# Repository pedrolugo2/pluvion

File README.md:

PLUVI.ON
--------

Como bons paulistanos, passamos pela mesma situação todos os anos. Chega dezembro, o céu escurece, a gente ouve um trovão lá no fundo, já dá aquele gelo na espinha pq a gente sabe que vem uma tempestade e provavelmente uma enchente por aí... E esse tipo de problema não acontece só em SP. 

Se olharmos Brasil, existem aproximadamente **30 milhões de brasileiros** expostos ao risco de enchentes e inundações. Além disso, existe uma projeção de impacto financeiro, onde as potenciais perdas anuais podem chegar a **4 bilhões de dólares até 2030** *(Fonte: Swiss Re)*

Olhando pra esse cenário alarmante, pensamos:
 “Vamos tentar resolver essa %$#@?” Se não para resolver totalmente, pelo menos entregar mais informação, mais inteligência para que a população possa se prevenir nesses eventos?
Resolvemos juntar nosso conhecimento de hardware e software e mergulhamos nesse mundo e logo de cara demos de cara com uma barreira: as dificuldades de conseguir informações sobre clima e chuva
Identificamos **3 principais desafios** relacionados à informação:

 1. As informações históricas são de difícil acesso ao cidadão comum (ou
    estão em mão de instituições privadas ou demandam muita burocracia
    dos órgãos públicos);
    
 2. Muitas delas são coletadas apenas no dia seguinte e portanto não auxiliam na
    prevenção 
    
 3. São informadas de forma genérica: “pode alagar a cidade de
    SP” – mas SP é grande demais para termos apenas essa informação. A
    probabilidade de alagar a Av. Paulista é sempre muito menor do que
    alagar a Av. Aricanduva

Foi a partir dessas hipóteses que construímos o Pluvi.On, uma estação meteorológica Open Source e de baixo custo para ser espalhada na maior quantidade de pontos da cidade que pudermos!!!

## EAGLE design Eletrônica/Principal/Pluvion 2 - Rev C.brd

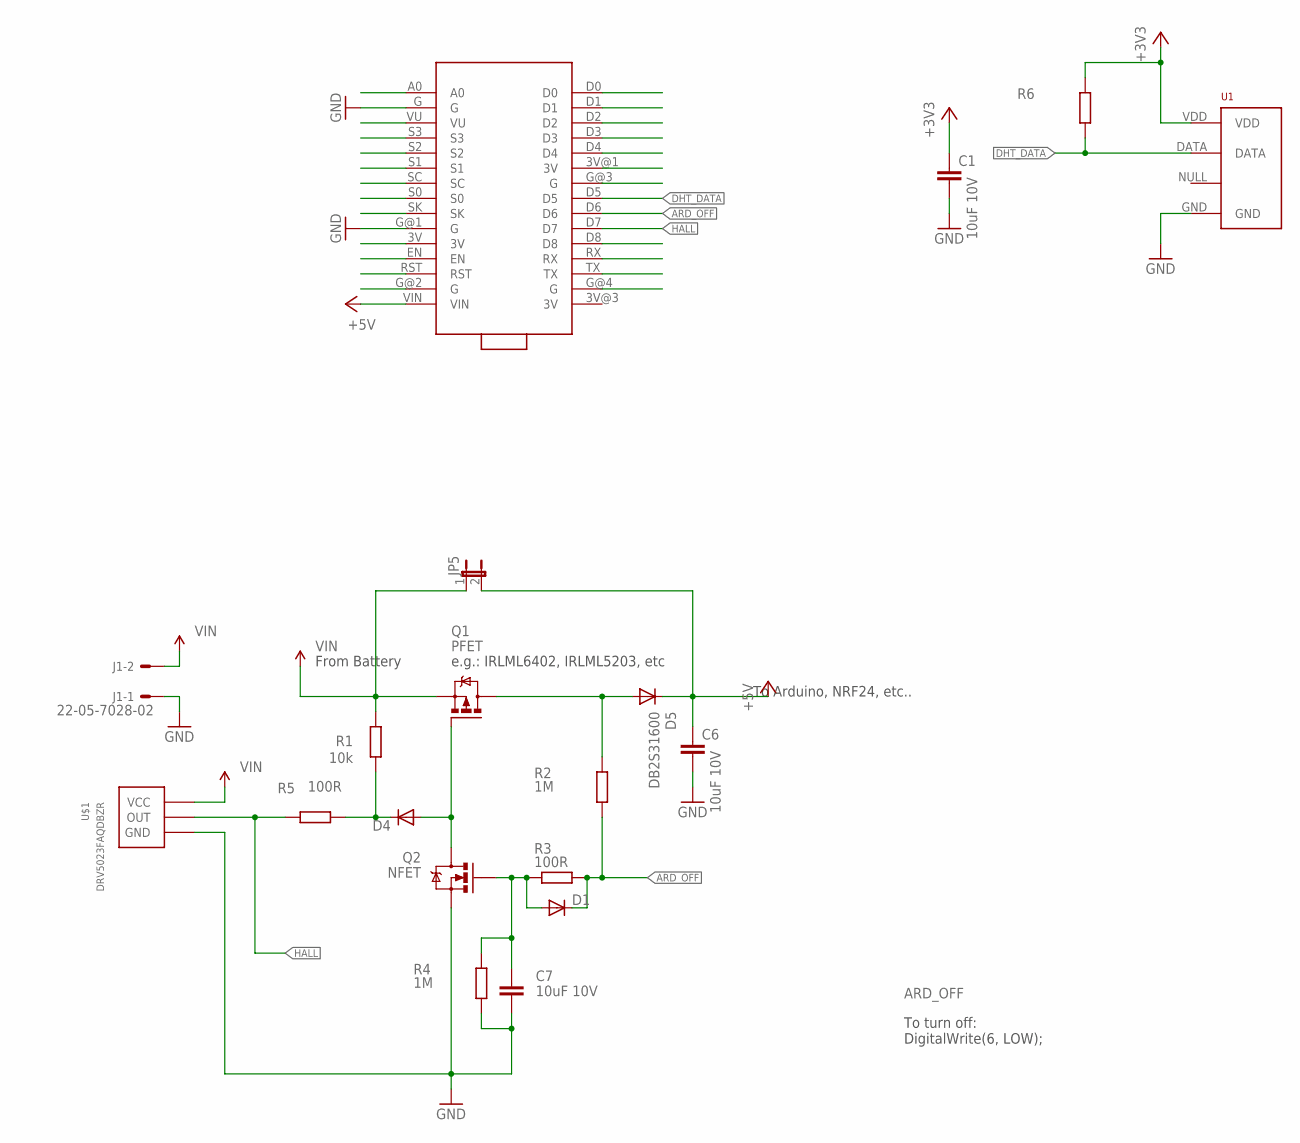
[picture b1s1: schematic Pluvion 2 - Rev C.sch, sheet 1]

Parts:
C1, C6, C7: 10uF 10V; C0805
D1, D4: DIODESOD; SOD-323
D5: DB2S31600; SMA-DIODE
J1: 22-05-7028-02; 7395-02
JP5: JUMPER-2PTH; 1X02
Q1: PFET; MICRO3
Q2: NFET; SOT23
R1: 10k; R0805
R2, R4: 1M; R0805
R3, R5: 100R; R0805
R6: R-EU_R0805; R0805
U1: RHT03_DHT-22_AM2302RA; RHT03_DHT-22/RA
U$1: DRV5023FAQDBZR; SOT23
U$2: NODE-LOLIN-ESP8266

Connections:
+3V3: C1.1, R6.2, U1.VDD, U$2.3V@1 (3V)
+5V: C6.1, D5.C, JP5.2, U$2.VIN
ARD_OFF: D1.1 (C), R2.1, R3.2, U$2.D6
BUTTONS: D4.2 (A), Q1.1 (G), Q2.3 (D)
DHT_DATA: R6.1, U1.DATA, U$2.D5
GND: C1.2, C6.2, C7.2, J1.1, Q2.2 (S), R4.1, U1.GND, U$1.3 (GND), U$2.G, U$2.G@1 (G)
HALL: R5.2, U$1.2 (OUT), U$2.D7
unnamed: D5.A, Q1.3 (D), R2.2
unnamed: C7.1, D1.2 (A), Q2.1 (G), R3.1, R4.2
unnamed: D4.1 (C), R1.1, R5.1
VIN: J1.2, JP5.1, Q1.2 (S), R1.2, U$1.1 (VCC)

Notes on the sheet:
e.g.: IRLML6402, IRLML5203, etc
To Arduino, NRF24, etc..
To turn off: DigitalWrite(6, LOW);
From Battery

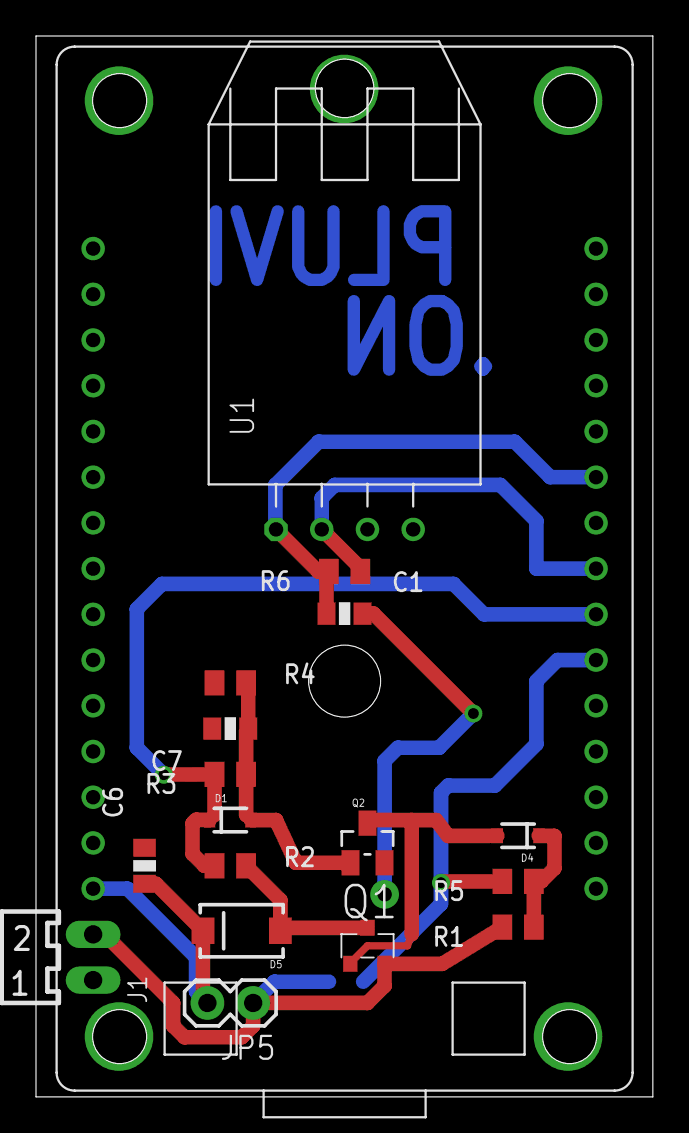
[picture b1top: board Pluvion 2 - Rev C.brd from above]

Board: 2 copper layers, 34.3 x 58.9 mm, 19 parts (1 on the bottom side), 11 nets.

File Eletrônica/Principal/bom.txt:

Partlist exported from C:/Users/Pedro/Desktop/05. Krafty/XX. Projetos/Pluvi.On/residencia/Eletrônica/Principal/Pluvion 2.sch at 26/09/2016 10:45

Qty Value              Device                    Package            Parts      Description                   MF MPN OC_FARNELL OC_NEWARK PROD_ID    
2                      DIODESOD                  SOD-323            D1, D4     Diode                                                     DIO-09646  
1                      JUMPER-2PTH               1X02               JP5        Jumper                                                               
1                      R-EU_R0805                R0805              R6         RESISTOR, European symbol                                            
1                      RHT03_DHT-22_AM2302RA     RHT03_DHT-22/RA    U1         RHT03 / DHT-22 / AM2302                                   SEN-10167  
2   100R               R-EU_R0805                R0805              R3, R5     RESISTOR, European symbol                                            
1   10k                R-EU_R0805                R0805              R1         RESISTOR, European symbol                                            
3   10uF 10V           C-EUC0805                 C0805              C1, C6, C7 CAPACITOR, European symbol                                           
2   1M                 R-EU_R0805                R0805              R2, R4     RESISTOR, European symbol                                            
1   22-05-7028-02      22-05-7028-02             7395-02            J1         CONNECTOR                            9731601    unknown              
1   DB2S31600          DIODESMA                  SMA-DIODE          D5         Diode                                                                
1   DRV5023FAQDBZR     DRV5023FAQDBZR            SOT23              U$1        Digital Switch Hall Sensor                                           
1   NFET               MOSFET-NCHANNELBSS123LT1G SOT23              Q2         Common NMOSFET Parts                                      TRANS-08345
1   NODE-LOLIN-ESP8266 NODE-LOLIN-ESP8266        NODE-LOLIN-ESP8266 U$2                                                                             
1   PFET               IRLML5203                 MICRO3             Q1         HEXFET P-Channel Power MOSFET

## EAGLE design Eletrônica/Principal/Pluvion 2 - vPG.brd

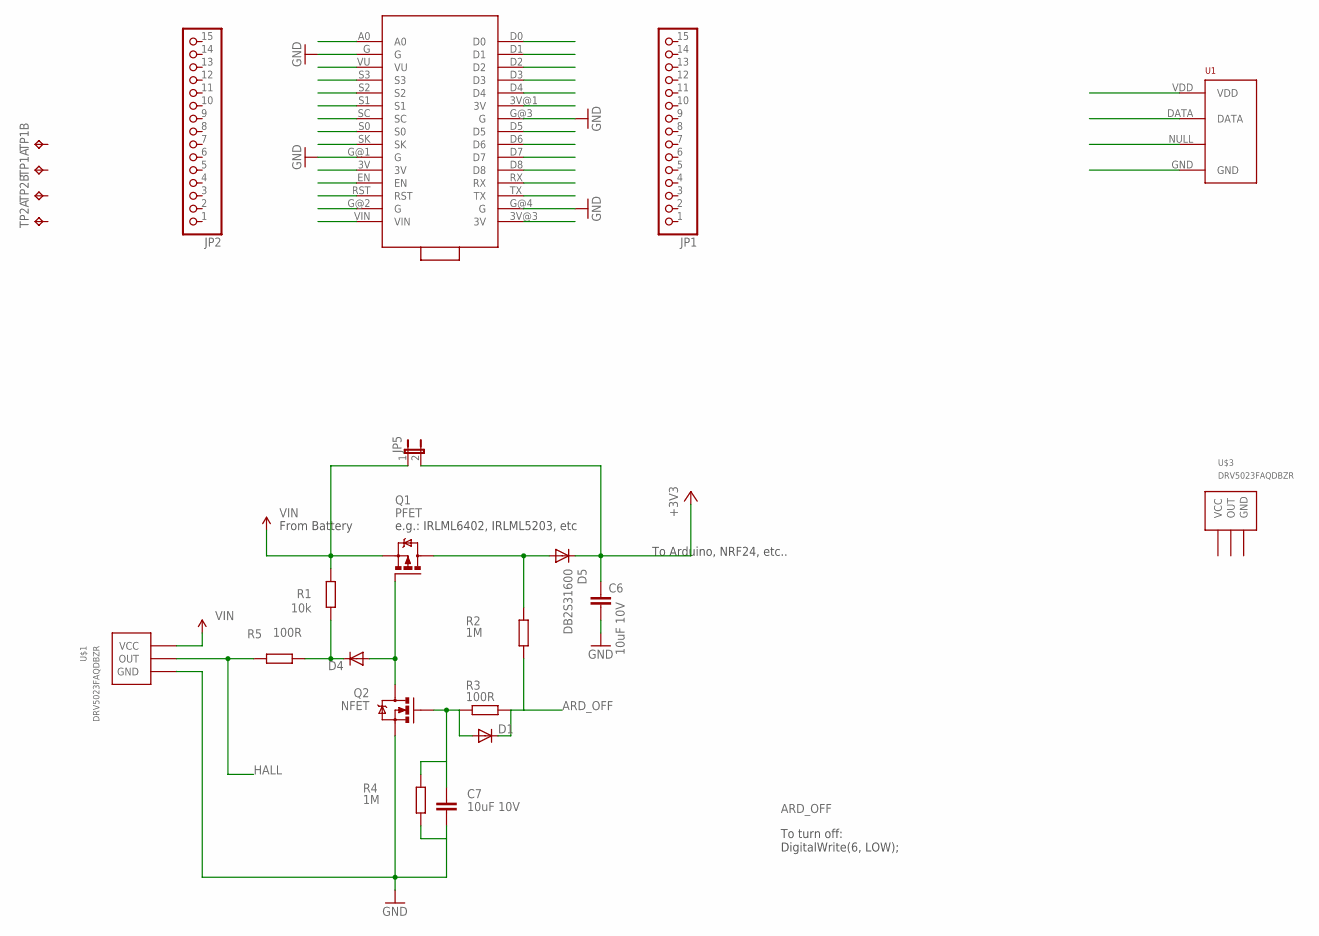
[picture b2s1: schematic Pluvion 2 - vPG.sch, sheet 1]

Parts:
C6, C7: 10uF 10V; C0805
D1, D4: DIODESMB; SMB-DIODE
D5: DB2S31600; SMB-DIODE
JP1, JP2: PINHD-1X15; 1X15
JP5: JUMPER-2PTH; 1X02
Q1: PFET; MICRO3
Q2: NFET; SOT23
R1: 10k; R0805
R2, R4: 1M; R0805
R3, R5: 100R; R0805
TP1, TP2: TP2P2-38-17; P2-38-17
U1: RHT03_DHT-22_AM2302RA; RHT03_DHT-22/RA
U$1, U$3: DRV5023FAQDBZR; SOT23
U$2: NODE-LOLIN-ESP8266

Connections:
+3V3: C6.1, D5.C, JP5.2
ARD_OFF: D1.C, R2.1, R3.2
BUTTONS: D4.A, Q1.1 (G), Q2.3 (D)
GND: C6.2, C7.2, Q2.2 (S), R4.1, U$1.3 (GND), U$2.G, U$2.G@1 (G), U$2.G@3 (G), U$2.G@4 (G)
HALL: R5.2, U$1.2 (OUT)
unnamed: D5.A, Q1.3 (D), R2.2
unnamed: C7.1, D1.A, Q2.1 (G), R3.1, R4.2
unnamed: D4.C, R1.1, R5.1
VIN: JP5.1, Q1.2 (S), R1.2, U$1.1 (VCC)

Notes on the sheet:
e.g.: IRLML6402, IRLML5203, etc
To Arduino, NRF24, etc..
To turn off: DigitalWrite(6, LOW);
From Battery

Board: 2 copper layers, 21 parts (0 on the bottom side), 9 nets, no tracks yet.

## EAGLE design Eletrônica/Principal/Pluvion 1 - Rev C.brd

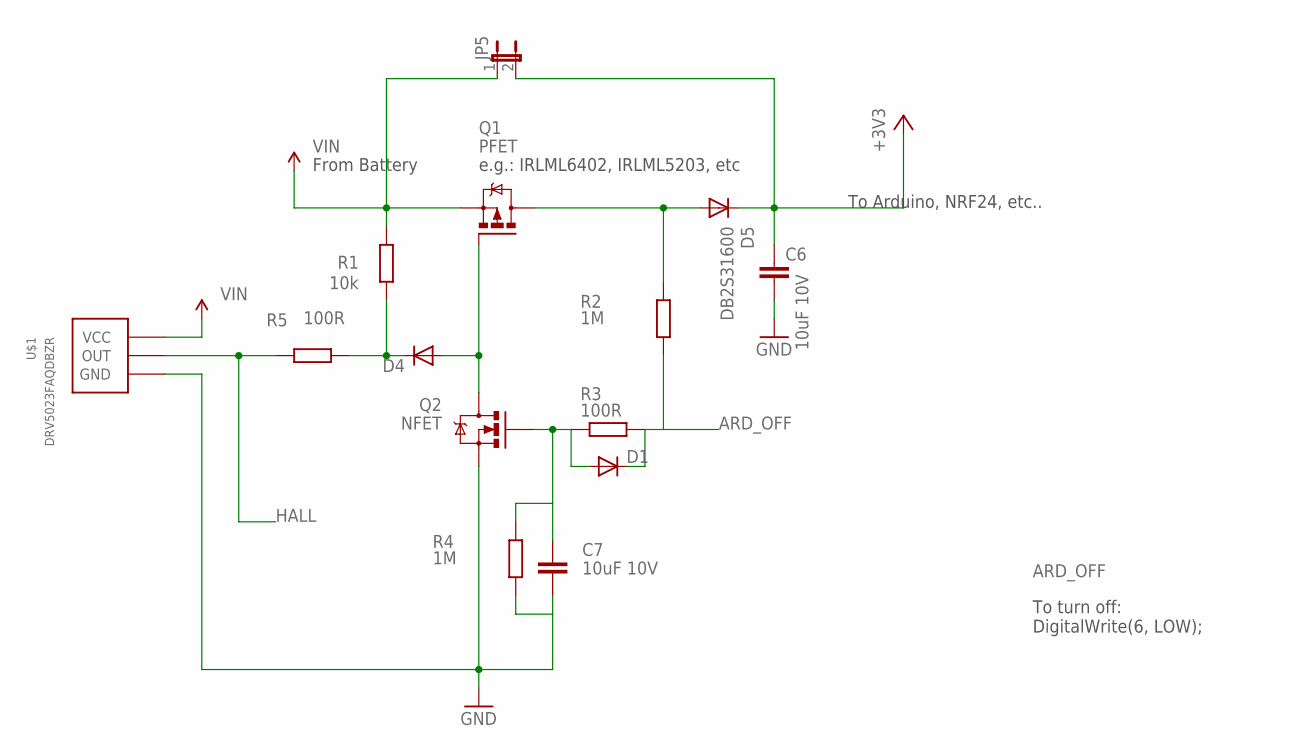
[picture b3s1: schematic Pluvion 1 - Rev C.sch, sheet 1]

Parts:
C6, C7: 10uF 10V; C0805
D1, D4: DIODESMB; SMB-DIODE
D5: DB2S31600; SMB-DIODE
JP5: JUMPER-2PTH; 1X02
Q1: PFET; MICRO3
Q2: NFET; SOT23
R1: 10k; R0805
R2, R4: 1M; R0805
R3, R5: 100R; R0805
U$1: DRV5023FAQDBZR; SOT23

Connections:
+3V3: C6.1, D5.C, JP5.2; also elsewhere on the board
ARD_OFF: D1.C, R2.1, R3.2; also elsewhere on the board
BUTTONS: D4.A, Q1.1 (G), Q2.3 (D)
GND: C6.2, C7.2, Q2.2 (S), R4.1, U$1.3 (GND); also elsewhere on the board
HALL: R5.2, U$1.2 (OUT)
unnamed: D5.A, Q1.3 (D), R2.2
unnamed: C7.1, D1.A, Q2.1 (G), R3.1, R4.2
unnamed: D4.C, R1.1, R5.1
VIN: JP5.1, Q1.2 (S), R1.2, U$1.1 (VCC)

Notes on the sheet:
e.g.: IRLML6402, IRLML5203, etc
To Arduino, NRF24, etc..
To turn off: DigitalWrite(6, LOW);
From Battery

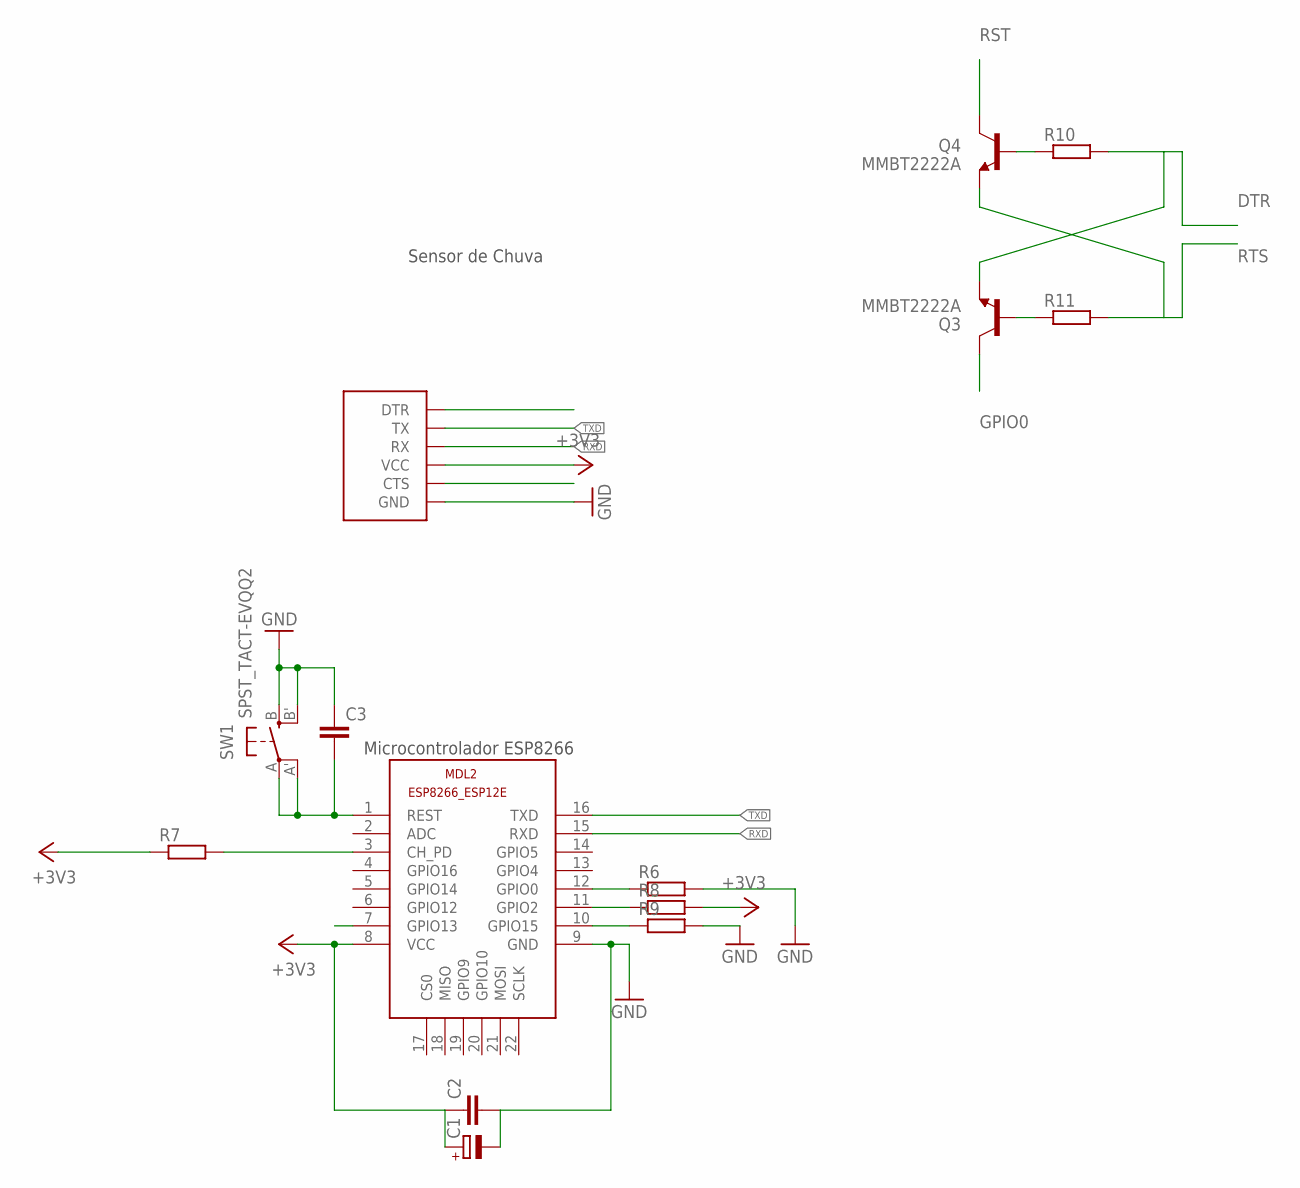
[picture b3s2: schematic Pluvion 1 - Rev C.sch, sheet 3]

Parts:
C1: CPOL-EUC; PANASONIC_C
C2, C3: C-EUC0805; C0805
MDL2: ESP8266-12EESP8266-ESP12E; ESP8266-ESP12E
Q3, Q4: MMBT2222A; SOT23
R6, R7, R8, R9, R10, R11: R-EU_R0805; R0805
SW1: SPST_TACT-EVQQ2; EVQ-Q2
U$2: FTDI_HEADERSMD; FTDI_HEADER_SMD

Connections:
+3V3: C1.+, C2.1, MDL2.8 (VCC), R7.1, R8.2, U$2.VCC; also elsewhere on the board
ARD_OFF: MDL2.7 (GPIO13); also elsewhere on the board
DTR: Q3.2 (E), R10.2, U$2.DTR
GND: C1.-, C2.2, C3.1, MDL2.9 (GND), R6.2, R9.2, SW1.B (S), SW1.B' (S1), U$2.GND; also elsewhere on the board
GPIO0: MDL2.12 (GPIO0), Q3.3 (C), R6.1
unnamed: C3.2, MDL2.1 (REST), SW1.A, SW1.A' (P1)
unnamed: MDL2.3 (CH_PD), R7.2
unnamed: MDL2.11 (GPIO2), R8.1
unnamed: MDL2.10 (GPIO15), R9.1
unnamed: Q3.1 (B), R11.1
unnamed: Q4.1 (B), R10.1
RST: Q4.3 (C)
RTS: Q4.2 (E), R11.2, U$2.CTS
RXD: MDL2.15 (RXD), U$2.RX
TXD: MDL2.16 (TXD), U$2.TX

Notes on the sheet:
Sensor de Chuva
Microcontrolador ESP8266

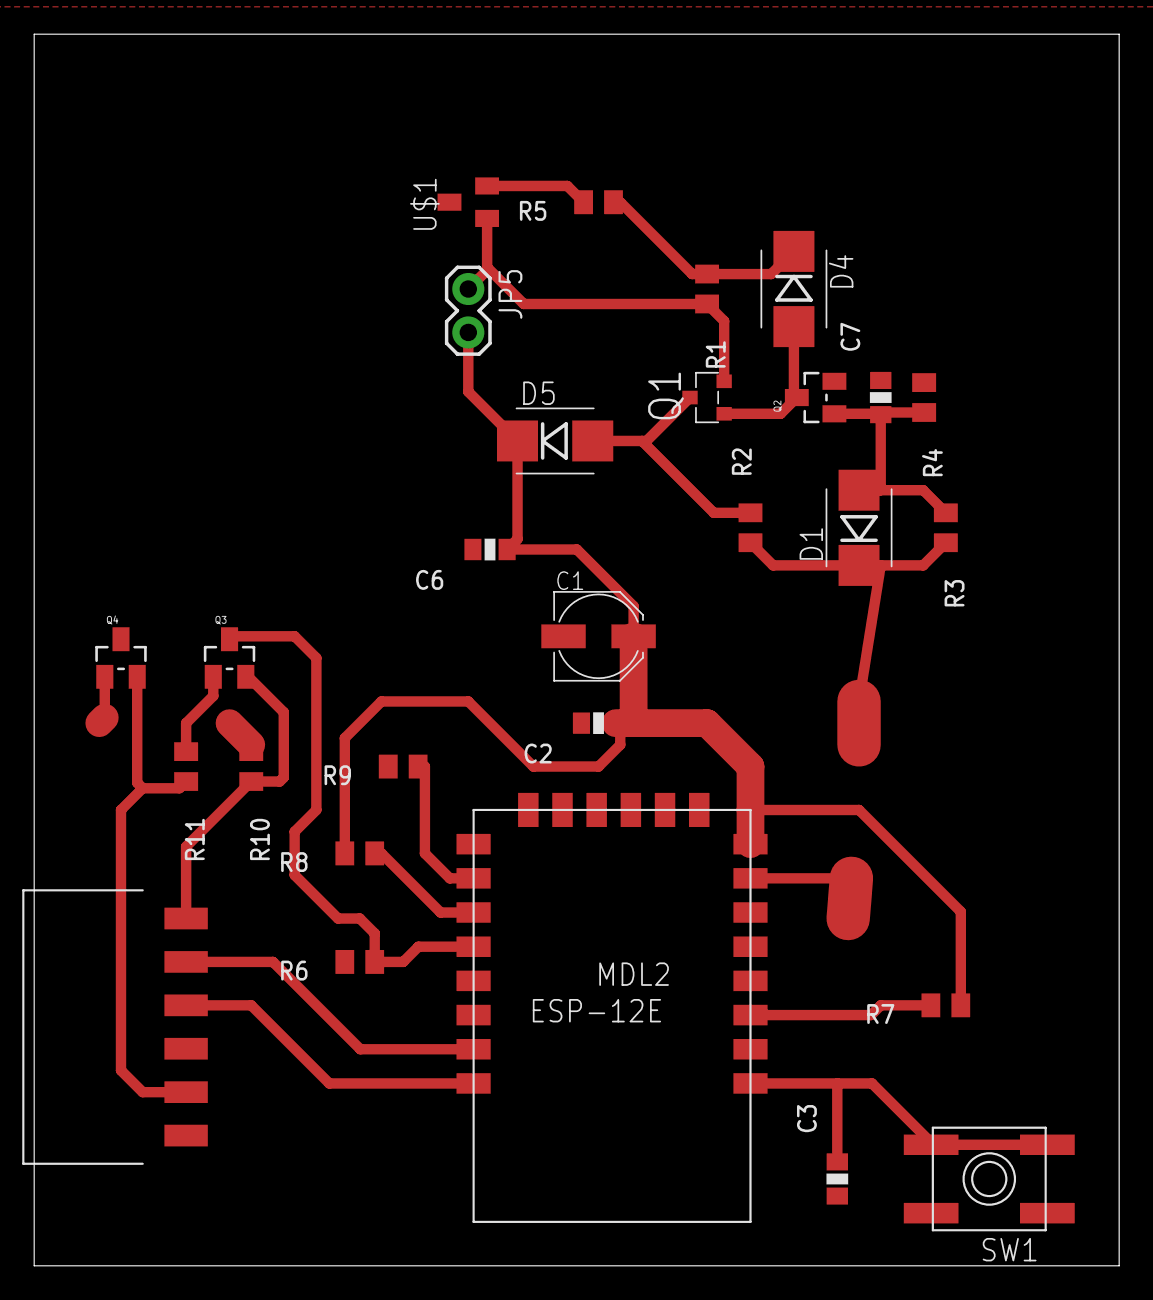
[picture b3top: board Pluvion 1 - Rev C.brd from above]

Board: 2 copper layers, 63.5 x 72.1 mm, 28 parts (0 on the bottom side), 20 nets.

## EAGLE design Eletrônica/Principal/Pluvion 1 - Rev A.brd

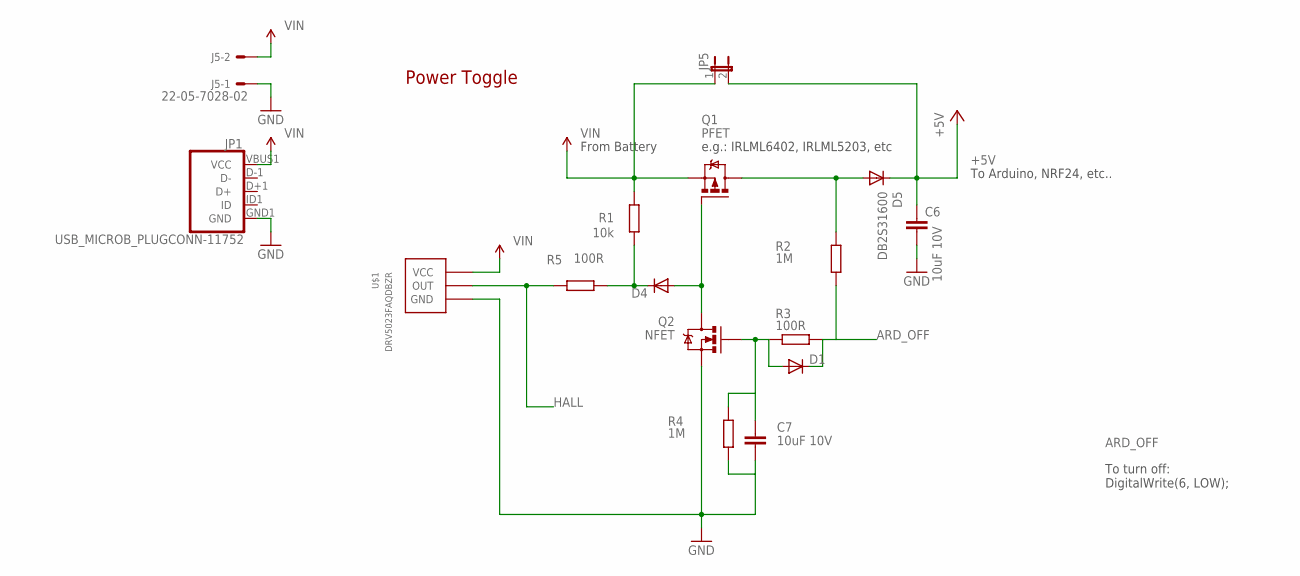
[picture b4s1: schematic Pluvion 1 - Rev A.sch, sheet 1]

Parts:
C6, C7: 10uF 10V; C0805
D1, D4: DIODESOD; SOD-323
D5: DB2S31600; SMA-DIODE
J5: 22-05-7028-02; 7395-02
JP1: USB_MICROB_PLUGCONN-11752; USB-B-MICRO-SMD_V03
JP5: JUMPER-2PTH; 1X02
Q1: PFET; MICRO3
Q2: NFET; SOT23
R1: 10k; R0805
R2, R4: 1M; R0805
R3, R5: 100R; R0805
U$1: DRV5023FAQDBZR; SOT23

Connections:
+5V: C6.1, D5.C, JP5.2; also elsewhere on the board
ARD_OFF: D1.1 (C), R2.1, R3.2
BUTTONS: D4.2 (A), Q1.1 (G), Q2.3 (D)
GND: C6.2, C7.2, J5.1, JP1.GND1 (GND), Q2.2 (S), R4.1, U$1.3 (GND); also elsewhere on the board
HALL: R5.2, U$1.2 (OUT); also elsewhere on the board
unnamed: D5.A, Q1.3 (D), R2.2
unnamed: C7.1, D1.2 (A), Q2.1 (G), R3.1, R4.2
unnamed: D4.1 (C), R1.1, R5.1
VIN: J5.2, JP1.VBUS1 (VCC), JP5.1, Q1.2 (S), R1.2, U$1.1 (VCC)

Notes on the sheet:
e.g.: IRLML6402, IRLML5203, etc
To Arduino, NRF24, etc..
To turn off: DigitalWrite(6, LOW);
From Battery
Power Toggle

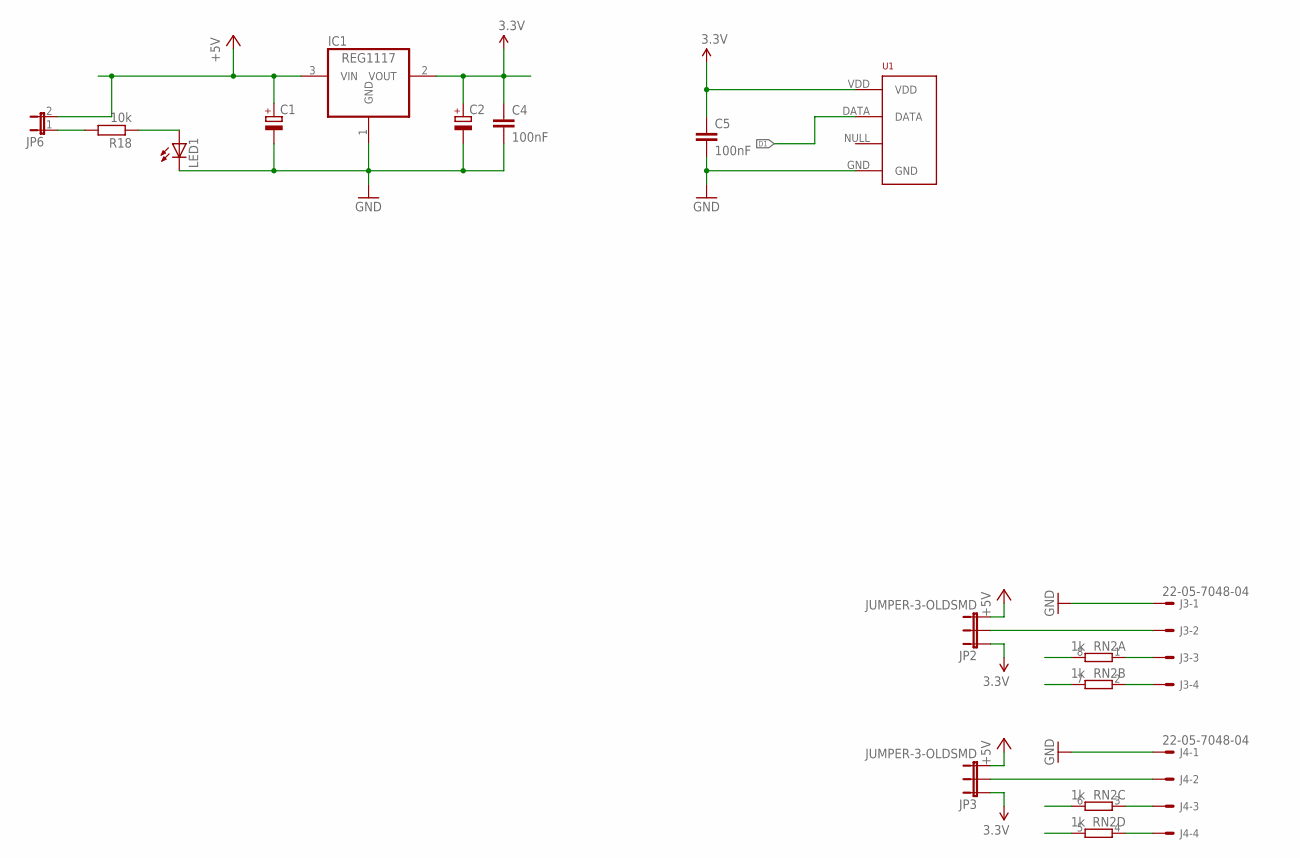
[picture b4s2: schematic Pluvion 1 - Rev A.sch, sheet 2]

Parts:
C1, C2: CPOL-EUC; PANASONIC_C
C4, C5: 100nF; C0805
IC1: REG1117; SOT223
J3, J4: 22-05-7048-04; 7395-04
JP2, JP3: JUMPER-3-OLDSMD; SJ_3
JP6: JUMPER-2SMD-NO; SJ_2S-NO
LED1: LED1206; LED-1206
R18: 10k; R0805
RN2: 1k; 0603-ARV
U1: RHT03_DHT-22_AM2302RA; RHT03_DHT-22/RA

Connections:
+3V3: C2.+, C4.1, C5.1, IC1.2 (VOUT), JP2.1, JP3.1, U1.VDD; also elsewhere on the board
+5V: C1.+, IC1.3 (VIN), JP2.3, JP3.3, JP6.2; also elsewhere on the board
D1: U1.DATA; also elsewhere on the board
GND: C1.-, C2.-, C4.2, C5.2, IC1.1 (GND), J3.1, J4.1, LED1.C, U1.GND; also elsewhere on the board
unnamed: J3.3, RN2.1
unnamed: J3.4, RN2.2 (1)
unnamed: J4.3, RN2.3 (1)
unnamed: J3.2, JP2.2
unnamed: J4.4, RN2.4 (1)
unnamed: J4.2, JP3.2
unnamed: LED1.A, R18.1
unnamed: JP6.1, R18.2

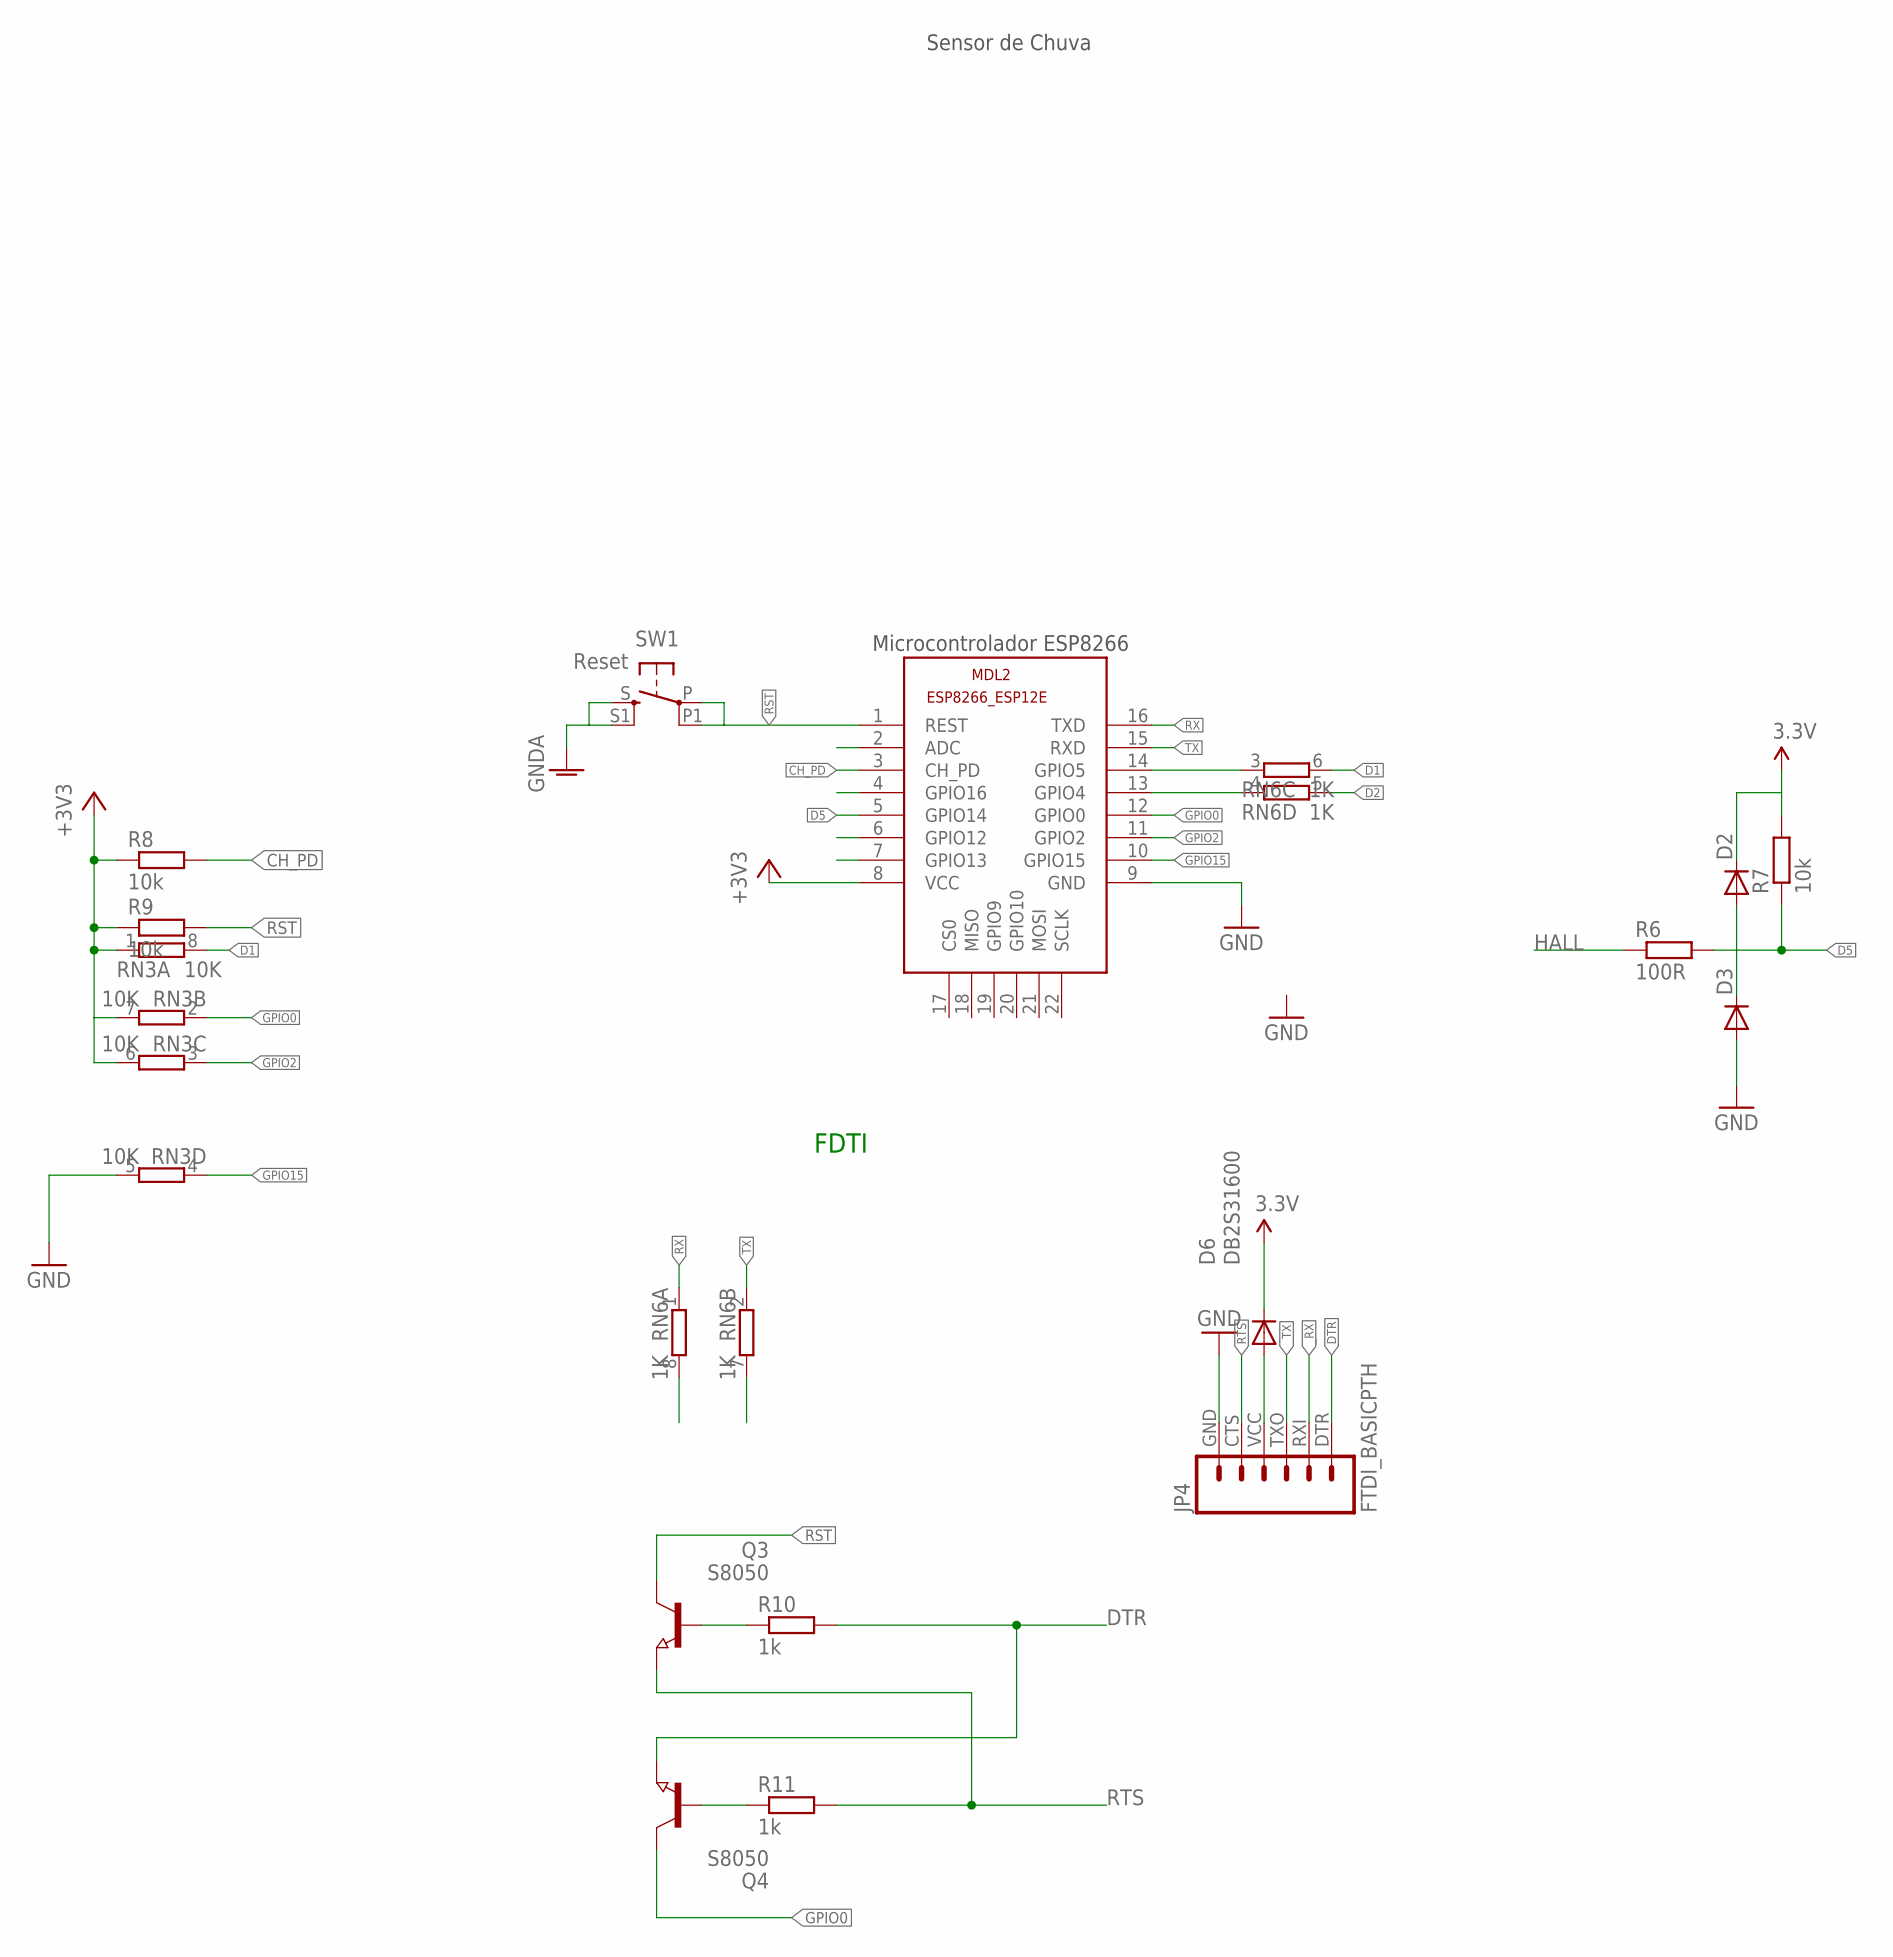
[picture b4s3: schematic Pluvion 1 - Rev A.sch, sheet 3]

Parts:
D2, D3: DIODESOD; SOD-323
D6: DB2S31600; SMA-DIODE
JP4: FTDI_BASICPTH; FTDI_BASIC
MDL2: ESP8266-12EESP8266-ESP12E; ESP8266-ESP12E
Q3, Q4: S8050; SOT23
R6: 100R; R0805
R7, R8, R9: 10k; R0805
R10, R11: 1k; R0805
RN3: 10K; 0603-ARV
RN6: 1K; 0603-ARV
SW1: Reset; BT4.5X4.5

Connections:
+3V3: D2.1 (C), D6.C, MDL2.8 (VCC), R7.2, R8.1, R9.1, RN3.1, RN3.6 (2), RN3.7 (2); also elsewhere on the board
CH_PD: MDL2.3 (CH_PD), R8.2
D1: RN3.8 (2), RN6.6 (2); also elsewhere on the board
D2: RN6.5 (2)
D5: D2.2 (A), D3.1 (C), MDL2.5 (GPIO14), R6.2, R7.1
DTR: JP4.DTR (1), Q4.2 (E), R10.2
GND: D3.2 (A), JP4.GND (6), MDL2.9 (GND), RN3.5 (2), SW1.S, SW1.S1; also elsewhere on the board
GPIO0: MDL2.12 (GPIO0), Q4.3 (C), RN3.2 (1)
GPIO2: MDL2.11 (GPIO2), RN3.3 (1)
GPIO15: MDL2.10 (GPIO15), RN3.4 (1)
HALL: R6.1; also elsewhere on the board
unnamed: Q3.1 (B), R10.1
unnamed: Q4.1 (B), R11.1
unnamed: MDL2.14 (GPIO5), RN6.3 (1)
unnamed: D6.A, JP4.VCC (4)
unnamed: MDL2.13 (GPIO4), RN6.4 (1)
RST: MDL2.1 (REST), Q3.3 (C), R9.2, SW1.P, SW1.P1
RTS: JP4.CTS (5), Q3.2 (E), R11.2
RX: MDL2.16 (TXD), RN6.1
TX: MDL2.15 (RXD), RN6.2 (1)
_RX: JP4.RXI (2), RN6.8 (2)
_TX: JP4.TXO (3), RN6.7 (2)

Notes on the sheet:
Sensor de Chuva
Microcontrolador ESP8266
FDTI

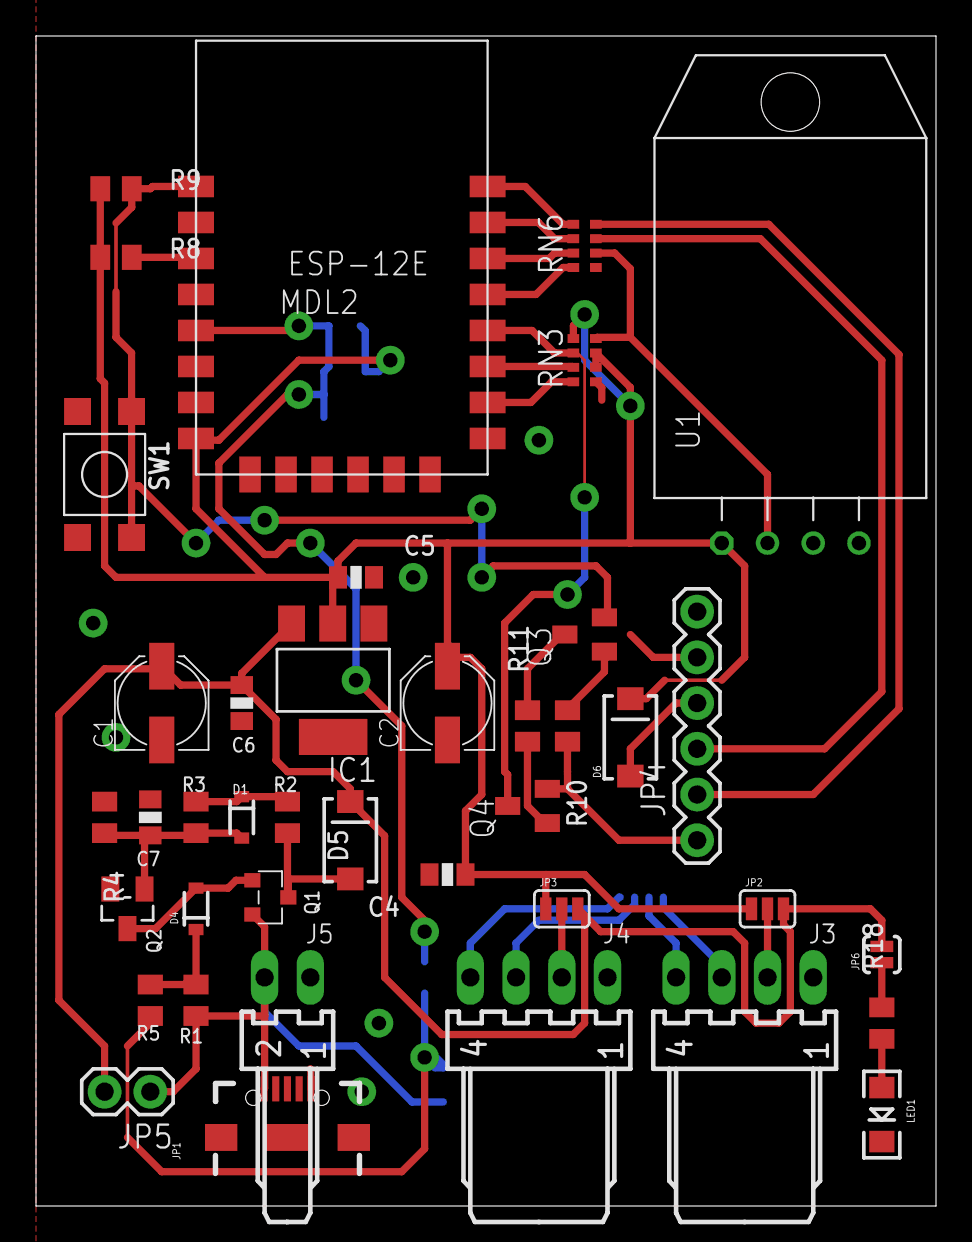
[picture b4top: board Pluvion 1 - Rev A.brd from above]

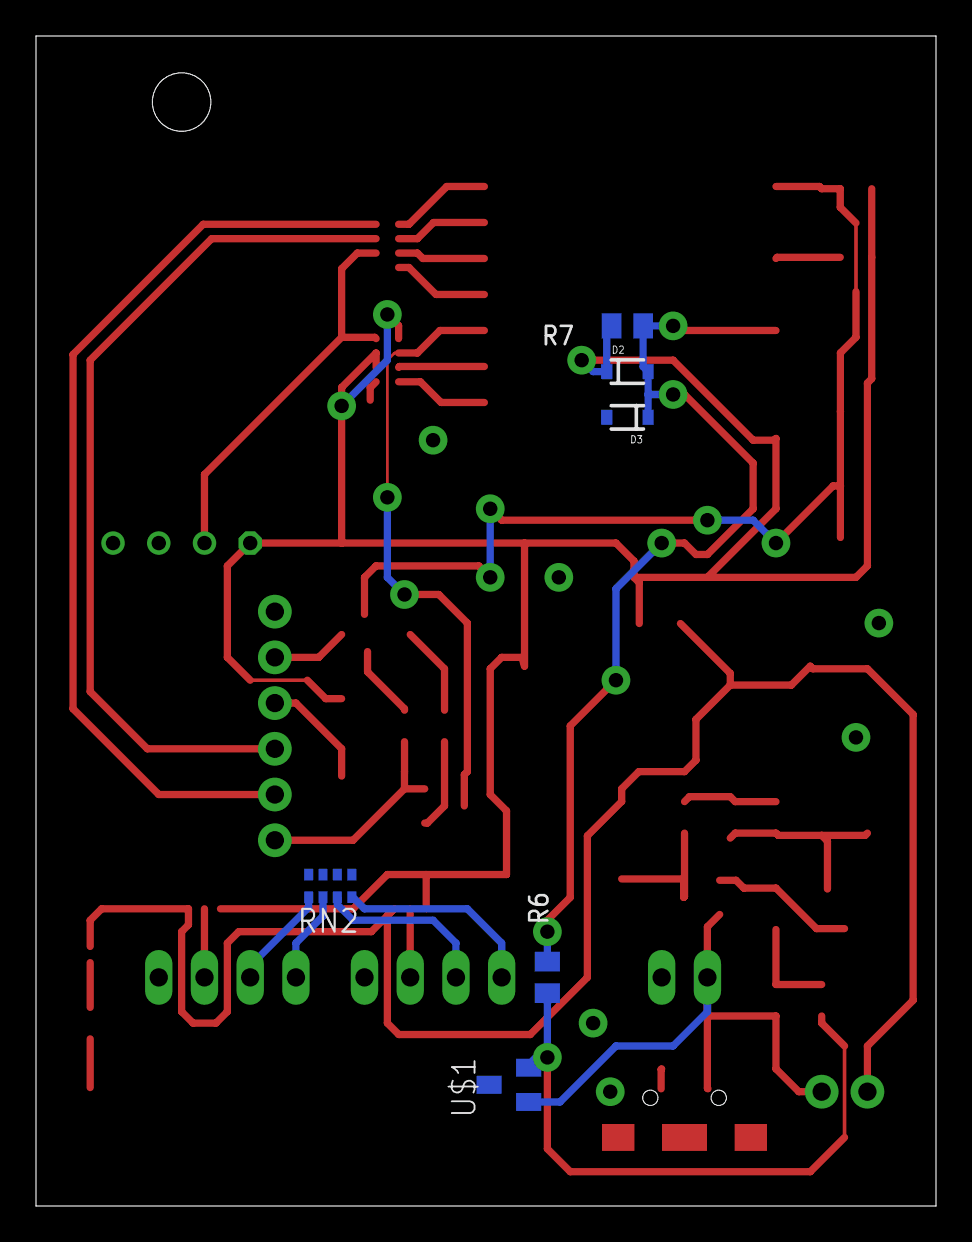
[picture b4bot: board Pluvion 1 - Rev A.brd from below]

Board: 2 copper layers, 50.0 x 65.0 mm, 46 parts (6 on the bottom side), 36 nets.

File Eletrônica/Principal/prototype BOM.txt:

Partlist exported from /Users/wes/Google Drive/trab/redbull/Residencia Basement/repo/Pluvion/Eletrônica/Principal/Pluvion 1 - Rev A.sch at 9/14/16 01:56

Assembly variant: ''

Qty Value                     Device                    Parts              
OK 2                             CPOL-EUC                  C1, C2             
OKISH 4                             DIODESOD                  D1, D2, D3, D4     
              
1                             JUMPER-2PTH               JP5                
                
1                             LED1206                   LED1               
                 
                 
1   1k                        4R-N0603-ARV              RN6, RN2   http://www.opoeneletronica.com.br/home/produto/codigo:12739/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
1   10k                       4R-N0603-ARV              RN3    http://www.opoeneletronica.com.br/home/produto/codigo:12686/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

OK 3   100R                      R-EU_R0805                R3, R5, R6
OK 2   1M                        R-EU_R0805                R2, R4    
OK 2   1k                        R-EU_R0805                R10, R11                          
OK 5   10k                       R-EU_R0805                R1, R7, R8, R9, R18

OK 2   10uF 10V                  C-EUC0805                 C6, C7 
OK 2   100nF                     C-EUC0805                 C4, C5





OK 2   DB2S31600                 DIODESMA                  D5, D6

1   DRV5023FAQDBZR            DRV5023FAQDBZR            U$1 

           
OK 1   NFET                      MOSFET-NCHANNELBSS123LT1G Q2                 
OK 1   PFET                      IRLML5203                 Q1                 
1   REG1117                   REG1117                   IC1  http://www.opoeneletronica.com.br/home/produto/codigo:14194/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

1   Reset                     10-XX-4.5SMD              SW1 

OK 2   S8050                     NPN-TRANSISTOR_SOT23      Q3, Q4

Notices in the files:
parts and their libraries:
SparkFun-DiscreteSemi: Licensing: CC v3.0 Share-Alike You are welcome to use this library for commercial purposes.
